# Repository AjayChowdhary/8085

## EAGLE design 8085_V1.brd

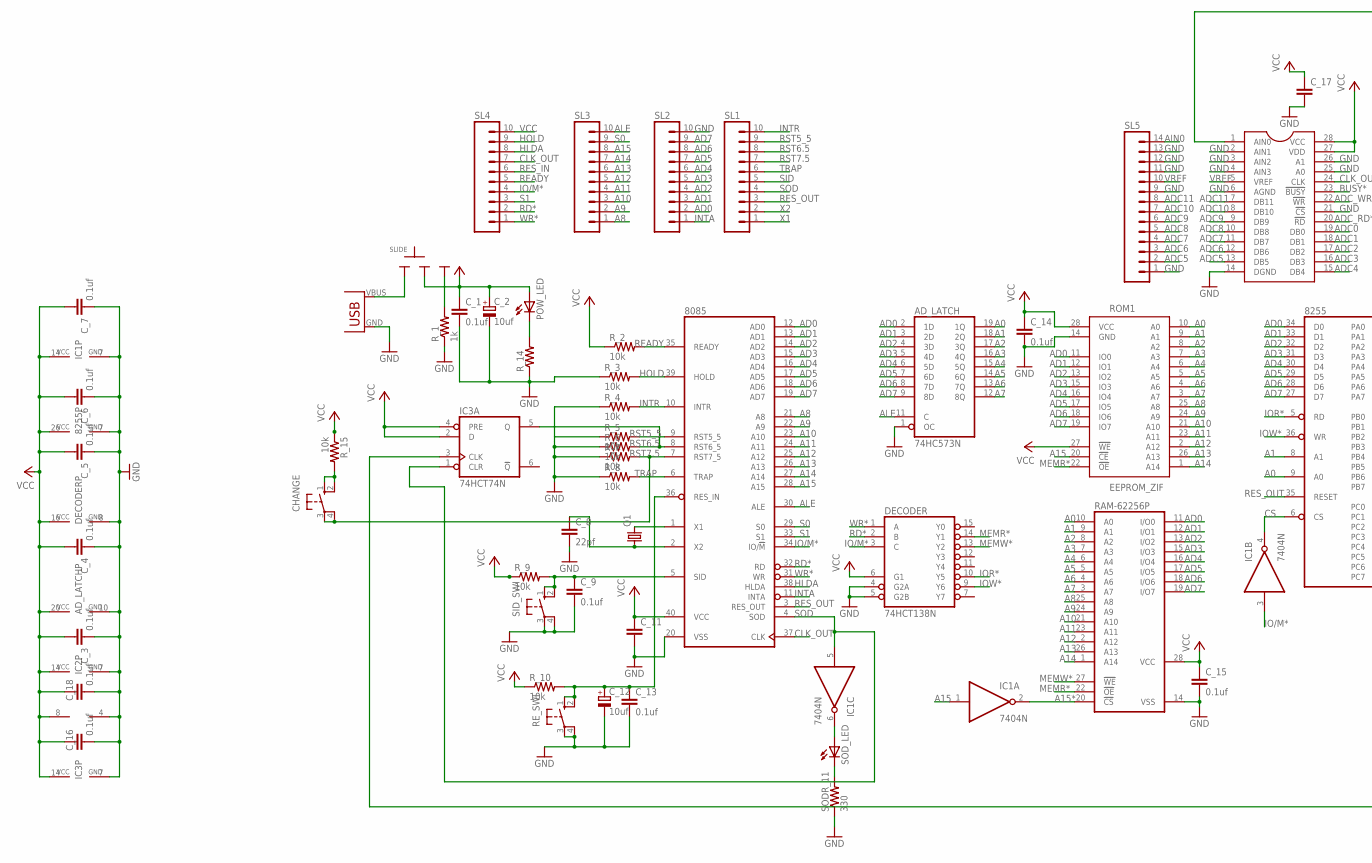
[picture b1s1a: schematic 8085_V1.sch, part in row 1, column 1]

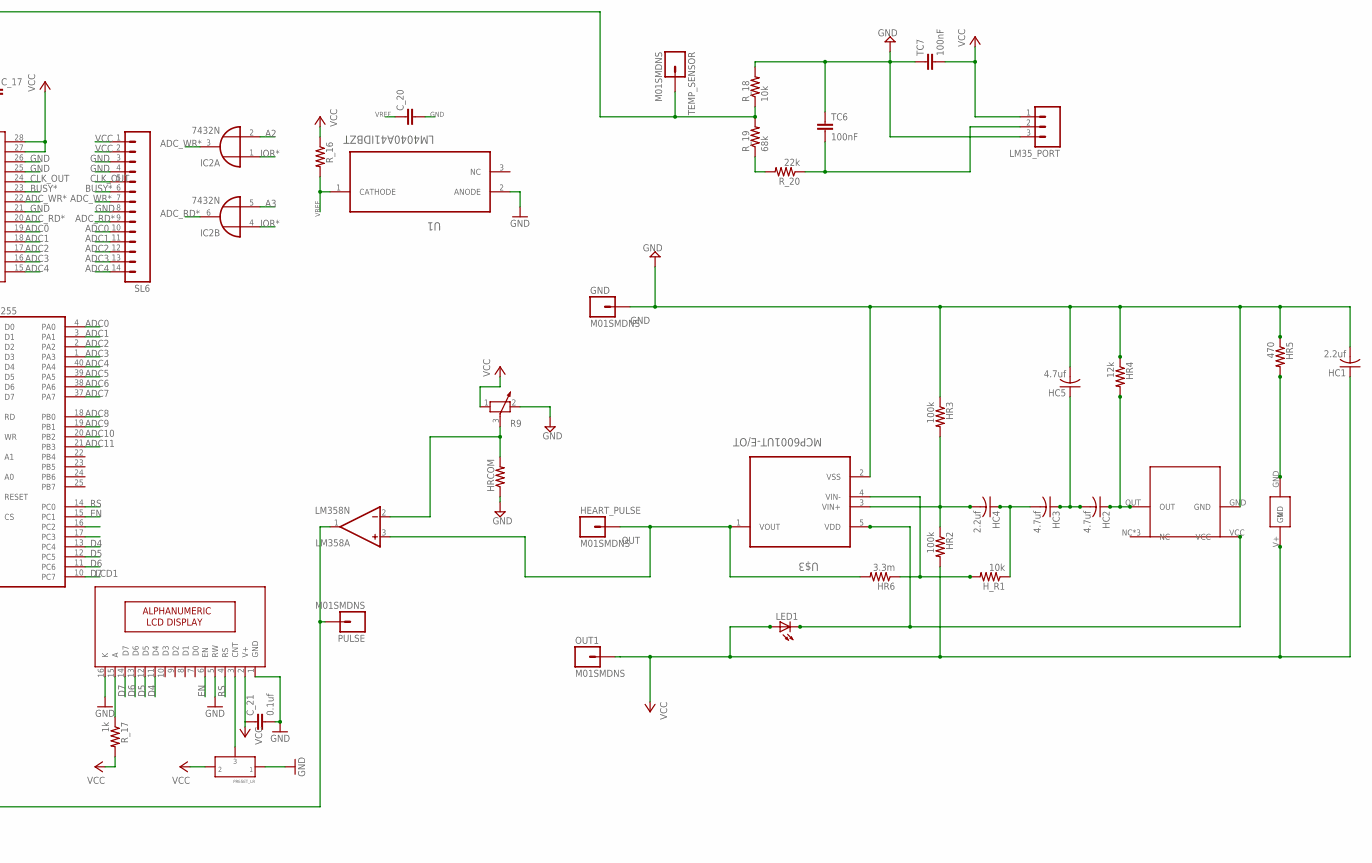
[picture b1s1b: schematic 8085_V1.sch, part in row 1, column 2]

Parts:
8085: 8085; DIL40
8255: 8255A; DIL40
ADC-1: ADS7842(12-ADC); SSOP28
AD_LATCH: 74HC573N; DIL20
CHANGE: 10-XX; B3F-10XX
C_1, C_3, C_4, C_5, C_6, C_7, C_16, C_18: 0.1uf; C025-025X050
C_2, C_12: 10uf; E2,5-5
C_8: 22pf; C025-024X044
C_9, C_13, C_14, C_15, C_21: 0.1uf; C025-024X044
C_11, C_17: C-EU025-024X044; C025-024X044
C_20: C-EU025-025X050; C025-025X050
DECODER: 74HCT138N; DIL16
FINGERLED: KBREVMTNLED; KBREVMNTLED
GND: M01SMDNS; 1X01NS
HC1, HC4: 2.2uf; C0402
HC2, HC3, HC5: 4.7uf; C0402
HEART_PULSE: M01SMDNS; 1X01NS
HR2, HR3: 100k; R0402
HR4: 12k; R0402
HR5: 470; R0402
HR6: 3.3m; R0402
HRCOM: R-US_0204/7; 0204/7
H_R1: 10k; R0402
IC1: 7404N; DIL14
IC2: 7432N; DIL14
IC3: 74HCT74N; DIL14
LCD1: 16X2LCD; 16X2_LCD
LED1: LEDCHIP-LED0603; CHIP-LED0603
LM35_PORT: M03; 03P
LM358: LM358N; DIL08
OUT1: M01SMDNS; 1X01NS
POW_LED: LED3MM
PULSE: M01SMDNS; 1X01NS
Q1: CRYSTALHC49US; HC49US
R9: POTENTIOMETER_PT-10; PT-10
RAM-62256P: 62256P; DIL28-6
RE_SWI: 10-XX; B3F-10XX
ROM1: EEPROM_ZIF; DIL28-6-ZIF_SOCKET
R_1, R_17: 1k; 0204/7
R_2, R_3, R_4, R_5, R_6, R_7, R_8, R_9, R_10, R_15, R_18: 10k; 0204/7
R_14: R-US_0204/7; 0204/7
R_16: RESISTOR0207/7; 0207/7
R_19: 68k; 0204/7
R_20: 22k; 0204/7
SID_SWI: 10-XX; B3F-10XX
SL1, SL2, SL3, SL4: M10; 10P
SL5, SL6: M14; 14P
SLIDE: SLIDESWITCH-BIG; BIGSWITCH
SODR_11: 330; 0204/7
SOD_LED: LED5MM
TC6, TC7: 100nF; C025-024X044
TEMP_SENSOR: M01SMDNS; 1X01NS
U1: LM4040A41IDBZT; SOT95P237X112-3N
U$1: PRESET_LR
U$2: USB(POWER)
U$3: MCP6001UT-E/OT; SOT95P270X145-5N
U$4: APDS9008

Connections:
A0: 8255.9 (A0), AD_LATCH.19 (1Q), RAM-62256P.10 (A0), ROM1.10 (A0)
A1: 8255.8 (A1), AD_LATCH.18 (2Q), RAM-62256P.9 (A1), ROM1.9 (A1)
A2: AD_LATCH.17 (3Q), IC2.2 (I1), RAM-62256P.8 (A2), ROM1.8 (A2)
A3: AD_LATCH.16 (4Q), IC2.5 (I1), RAM-62256P.7 (A3), ROM1.7 (A3)
A4: AD_LATCH.15 (5Q), RAM-62256P.6 (A4), ROM1.6 (A4)
A5: AD_LATCH.14 (6Q), RAM-62256P.5 (A5), ROM1.5 (A5)
A6: AD_LATCH.13 (7Q), RAM-62256P.4 (A6), ROM1.4 (A6)
A7: AD_LATCH.12 (8Q), RAM-62256P.3 (A7), ROM1.3 (A7)
A8: 8085.21 (A8), RAM-62256P.25 (A8), ROM1.25 (A8), SL3.1
A9: 8085.22 (A9), RAM-62256P.24 (A9), ROM1.24 (A9), SL3.2
A10: 8085.23 (A10), RAM-62256P.21 (A10), ROM1.21 (A10), SL3.3
A11: 8085.24 (A11), RAM-62256P.23 (A11), ROM1.23 (A11), SL3.4
A12: 8085.25 (A12), RAM-62256P.2 (A12), ROM1.2 (A12), SL3.5
A13: 8085.26 (A13), RAM-62256P.26 (A13), ROM1.26 (A13), SL3.6
A14: 8085.27 (A14), RAM-62256P.1 (A14), ROM1.1 (A14), SL3.7
A15: 8085.28 (A15), IC1.1 (I), ROM1.20 (!CE), SL3.8
A15*: IC1.2 (O), RAM-62256P.20 (!CS)
AD0: 8085.12 (AD0), 8255.34 (D0), AD_LATCH.2 (1D), RAM-62256P.11 (I/O0), ROM1.11 (IO0), SL2.2
AD1: 8085.13 (AD1), 8255.33 (D1), AD_LATCH.3 (2D), RAM-62256P.12 (I/O1), ROM1.12 (IO1), SL2.3
AD2: 8085.14 (AD2), 8255.32 (D2), AD_LATCH.4 (3D), RAM-62256P.13 (I/O2), ROM1.13 (IO2), SL2.4
AD3: 8085.15 (AD3), 8255.31 (D3), AD_LATCH.5 (4D), RAM-62256P.15 (I/O3), ROM1.15 (IO3), SL2.5
AD4: 8085.16 (AD4), 8255.30 (D4), AD_LATCH.6 (5D), RAM-62256P.16 (I/O4), ROM1.16 (IO4), SL2.6
AD5: 8085.17 (AD5), 8255.29 (D5), AD_LATCH.7 (6D), RAM-62256P.17 (I/O5), ROM1.17 (IO5), SL2.7
AD6: 8085.18 (AD6), 8255.28 (D6), AD_LATCH.8 (7D), RAM-62256P.18 (I/O6), ROM1.18 (IO6), SL2.8
AD7: 8085.19 (AD7), 8255.27 (D7), AD_LATCH.9 (8D), RAM-62256P.19 (I/O7), ROM1.19 (IO7), SL2.9
ADC0: 8255.4 (PA0), ADC-1.19 (DB0), SL6.10
ADC1: 8255.3 (PA1), ADC-1.18 (DB1), SL6.11
ADC2: 8255.2 (PA2), ADC-1.17 (DB2), SL6.12
ADC3: 8255.1 (PA3), ADC-1.16 (DB3), SL6.13
ADC4: 8255.40 (PA4), ADC-1.15 (DB4), SL6.14
ADC5: 8255.39 (PA5), ADC-1.13 (DB5), SL5.2
ADC6: 8255.38 (PA6), ADC-1.12 (DB6), SL5.3
ADC7: 8255.37 (PA7), ADC-1.11 (DB7), SL5.4
ADC8: 8255.18 (PB0), ADC-1.10 (DB8), SL5.5
ADC9: 8255.19 (PB1), ADC-1.9 (DB9), SL5.6
ADC10: 8255.20 (PB2), ADC-1.8 (DB10), SL5.7
ADC11: 8255.21 (PB3), ADC-1.7 (DB11), SL5.8
ADC_RD*: ADC-1.20 (!RD), IC2.6 (O), SL6.9
ADC_WR*: ADC-1.22 (!WR), IC2.3 (O), SL6.7
AIN0: SL5.14
ALE: 8085.30 (ALE), AD_LATCH.11 (C), SL3.10
BUSY*: ADC-1.23 (!BUSY), SL6.6
CLK_OUT: 8085.37 (CLK), ADC-1.24 (CLK), SL4.7, SL6.5
CS: 8255.6 (CS), IC1.4 (O)
D4: 8255.13 (PC4), LCD1.11 (D4)
D5: 8255.12 (PC5), LCD1.12 (D5)
D6: 8255.11 (PC6), LCD1.13 (D6)
D7: 8255.10 (PC7), LCD1.14 (D7)
EN: 8255.15 (PC1), LCD1.6 (EN)
GND: 8085.20 (VSS), 8255.7 (GND), ADC-1.2 (AIN1), ADC-1.3 (AIN2), ADC-1.4 (AIN3), ADC-1.6 (AGND), ADC-1.14 (DGND), ADC-1.21 (!CS), ADC-1.25 (A0), ADC-1.26 (A1), AD_LATCH.1 (OC), AD_LATCH.10 (GND), C_1.2, C_2.-, C_3.2, C_4.2, C_5.2, C_6.2, C_7.2, C_8.2, C_9.2, C_11.2, C_12.-, C_13.2, C_14.2, C_15.2, C_16.2, C_17.2, C_18.2, C_20.2, C_21.2, DECODER.4 (G2A), DECODER.5 (G2B), DECODER.8 (GND), GND.1, HC1.2, HC5.2, HR3.1, HR4.1, HR5.1, HRCOM.1, IC1.7 (GND), IC2.7 (GND), IC3.7 (GND), LCD1.1 (GND), LCD1.5 (RW), LCD1.16 (K), LM35_PORT.3, LM358.4 (V-), R9.2, RAM-62256P.14 (VSS), RE_SWI.3, RE_SWI.4 (P1), ROM1.14 (GND), R_1.1, R_3.1, R_4.1, R_5.1, R_6.1, R_7.1, R_8.1, R_14.1, R_18.2, SID_SWI.3, SID_SWI.4 (P1), SL2.10, SL5.1, SL5.9, SL5.11, SL5.12, SL5.13, SL6.3, SL6.4, SL6.8, SODR_11.1, TC6.1, TC7.1, U1.2 (ANODE), U$1.P$1 (1), U$2.GND, U$3.2 (VSS), U$4.GND
HLDA: 8085.38 (HLDA), SL4.8
HOLD: 8085.39 (HOLD), R_3.2, SL4.9
INTA: 8085.11 (INTA), SL2.1
INTR: 8085.10 (INTR), R_4.2, SL1.10
IO/M*: 8085.34 (IO/!M), DECODER.3 (C), IC1.3 (I), SL4.4
IOR*: 8255.5 (RD), DECODER.10 (Y5), IC2.1 (I0), IC2.4 (I0)
IOW*: 8255.36 (WR), DECODER.9 (Y6)
MEMR*: DECODER.14 (Y1), RAM-62256P.22 (!OE), ROM1.22 (!OE)
MEMW*: DECODER.13 (Y2), RAM-62256P.27 (!WE)
unnamed: SODR_11.2, SOD_LED.K (C)
unnamed: POW_LED.K (C), R_14.2
unnamed: IC1.6 (O), SOD_LED.A
unnamed: LED1.C, U$3.5 (VDD), U$4.VCC
unnamed: HC2.2, HC3.1, HC5.1
unnamed: HC3.2, HC4.1, H_R1.1
unnamed: HC4.2, HR2.1, HR3.2, U$3.3 (VIN+)
unnamed: HR6.1, H_R1.2, U$3.4 (VIN-)
unnamed: HC2.1, HR4.2, U$4.OUT
unnamed: FINGERLED.GND, HR5.2
unnamed: ADC-1.1 (AIN0), R_18.1, R_19.2, TEMP_SENSOR.1
unnamed: LM35_PORT.2, R_20.1, TC6.2
unnamed: LCD1.3 (CNT), U$1.P$3 (3)
unnamed: R_19.1, R_20.2
unnamed: HRCOM.2, LM358.2 (-IN), R9.3
unnamed: IC3.3 (CLK), LM358.1 (OUT), PULSE.1
unnamed: LCD1.15 (A), R_17.1
unnamed: SLIDE.1, U$2.VBUS (VCC)
unnamed: R_1.2, SLIDE.3
OUT: HEART_PULSE.1, HR6.2, LM358.3 (+IN), U$3.1 (VOUT)
RD*: 8085.32 (RD), DECODER.2 (B), SL4.2
READY: 8085.35 (READY), R_2.2, SL4.5
RES_IN: 8085.36 (RES_IN), C_12.+, C_13.1, RE_SWI.1 (S), RE_SWI.2 (S1), R_10.2, SL4.6
RES_OUT: 8085.3 (RES_OUT), 8255.35 (RESET), SL1.3
RS: 8255.14 (PC0), LCD1.4 (RS)
RST5_5: 8085.9 (RST5_5), R_5.2, SL1.9
RST6.5: 8085.8 (RST6_5), IC3.5 (Q), R_6.2, SL1.8
RST7.5: 8085.7 (RST7_5), CHANGE.3, CHANGE.4 (P1), R_7.2, SL1.7
S0: 8085.29 (S0), SL3.9
S1: 8085.33 (S1), SL4.3
SID: 8085.5 (SID), C_9.1, R_9.2, SID_SWI.1 (S), SID_SWI.2 (S1), SL1.5
SID1: CHANGE.1 (S), CHANGE.2 (S1), R_15.2
SOD: 8085.4 (SOD), IC1.5 (I), IC3.1 (CLR), SL1.4
TRAP: 8085.6 (TRAP), R_8.2, SL1.6
VCC: 8085.40 (VCC), 8255.26 (VCC), ADC-1.27 (VDD), ADC-1.28 (VCC), AD_LATCH.20 (VCC), C_1.1, C_2.+, C_3.1, C_4.1, C_5.1, C_6.1, C_7.1, C_11.1, C_14.1, C_15.1, C_16.1, C_17.1, C_18.1, C_21.1, DECODER.6 (G1), DECODER.16 (VCC), FINGERLED.V+ (V), HC1.1, HR2.2, IC1.14 (VCC), IC2.14 (VCC), IC3.2 (D), IC3.4 (PRE), IC3.14 (VCC), LCD1.2 (V+), LED1.A, LM35_PORT.1, LM358.8 (V+), OUT1.1, POW_LED.A, R9.1, RAM-62256P.28 (VCC), ROM1.27 (!WE), ROM1.28 (VCC), R_2.1, R_9.1, R_10.1, R_15.1, R_16.1, R_17.2, SL4.10, SL6.1, SL6.2, SLIDE.2, TC7.2, U$1.P$2 (2)
VREF: ADC-1.5 (VREF), C_20.1, R_16.2, SL5.10, U1.1 (CATHODE)
WR*: 8085.31 (WR), DECODER.1 (A), SL4.1
X1: 8085.1 (X1), Q1.2, SL1.1
X2: 8085.2 (X2), C_8.1, Q1.1, SL1.2

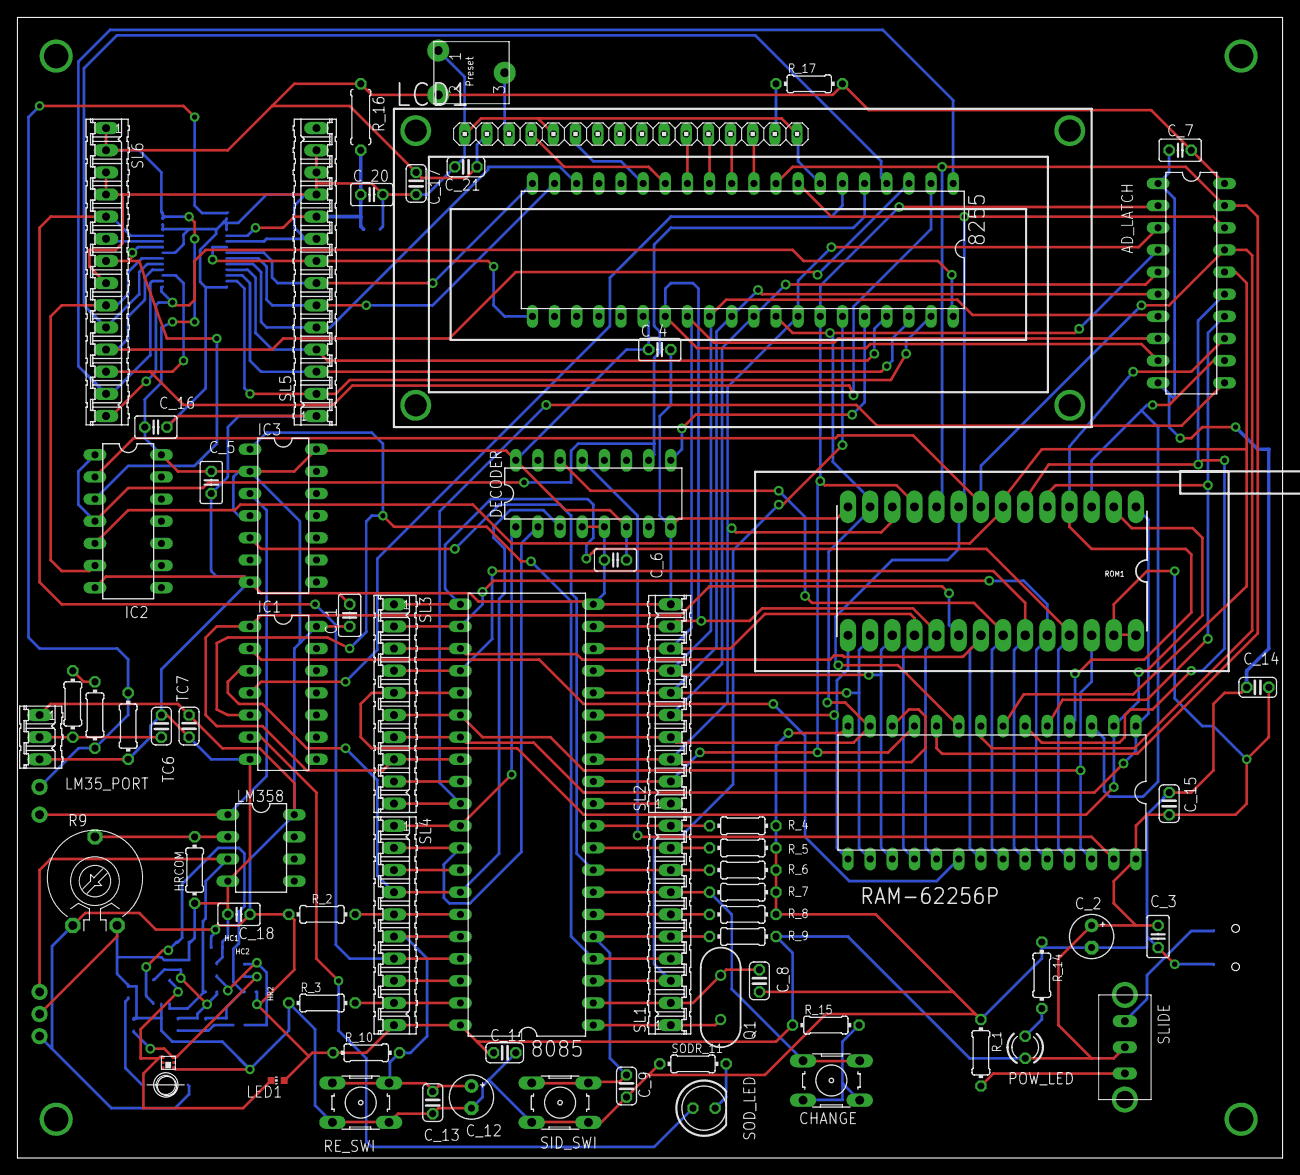
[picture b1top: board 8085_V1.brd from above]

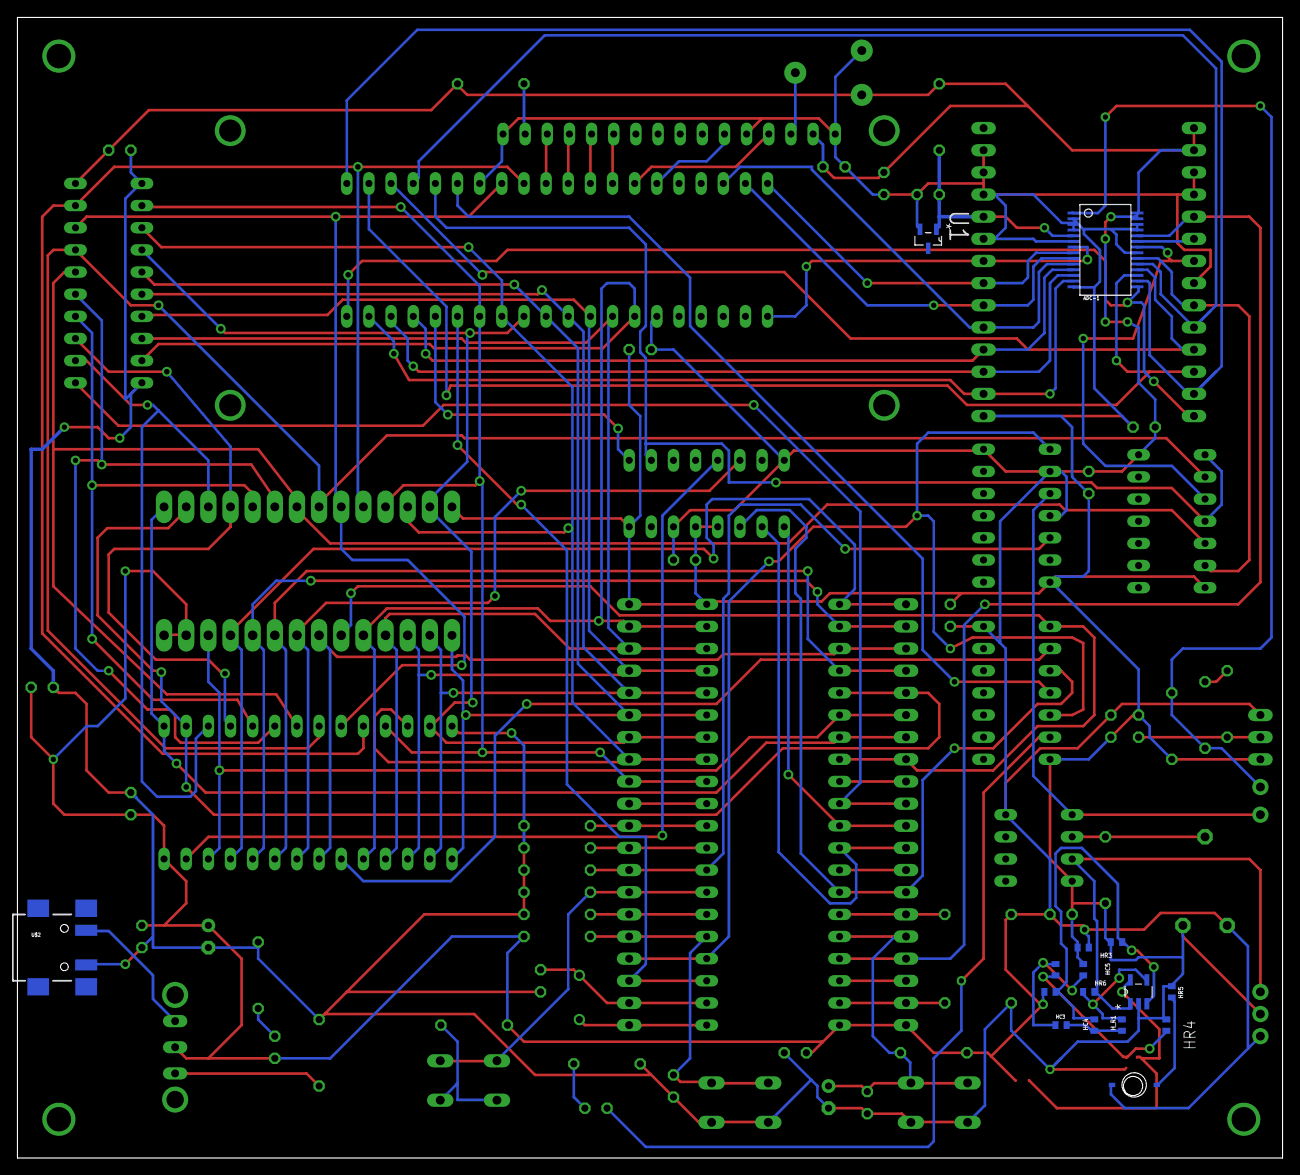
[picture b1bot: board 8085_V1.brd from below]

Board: 2 copper layers, 145.1 x 130.8 mm, 90 parts (15 on the bottom side), 97 nets.

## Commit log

2017-04-24 :lollipop: Added .gitattributes & .gitignore files
2017-04-24 8085V1
2017-04-25 26/4
2017-04-25 Gerber_files
2017-09-04 final report

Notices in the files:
parts and their libraries:
SparkFun: Licensing: CC v3.0 Share-Alike You are welcome to use this library for commercial purposes.
